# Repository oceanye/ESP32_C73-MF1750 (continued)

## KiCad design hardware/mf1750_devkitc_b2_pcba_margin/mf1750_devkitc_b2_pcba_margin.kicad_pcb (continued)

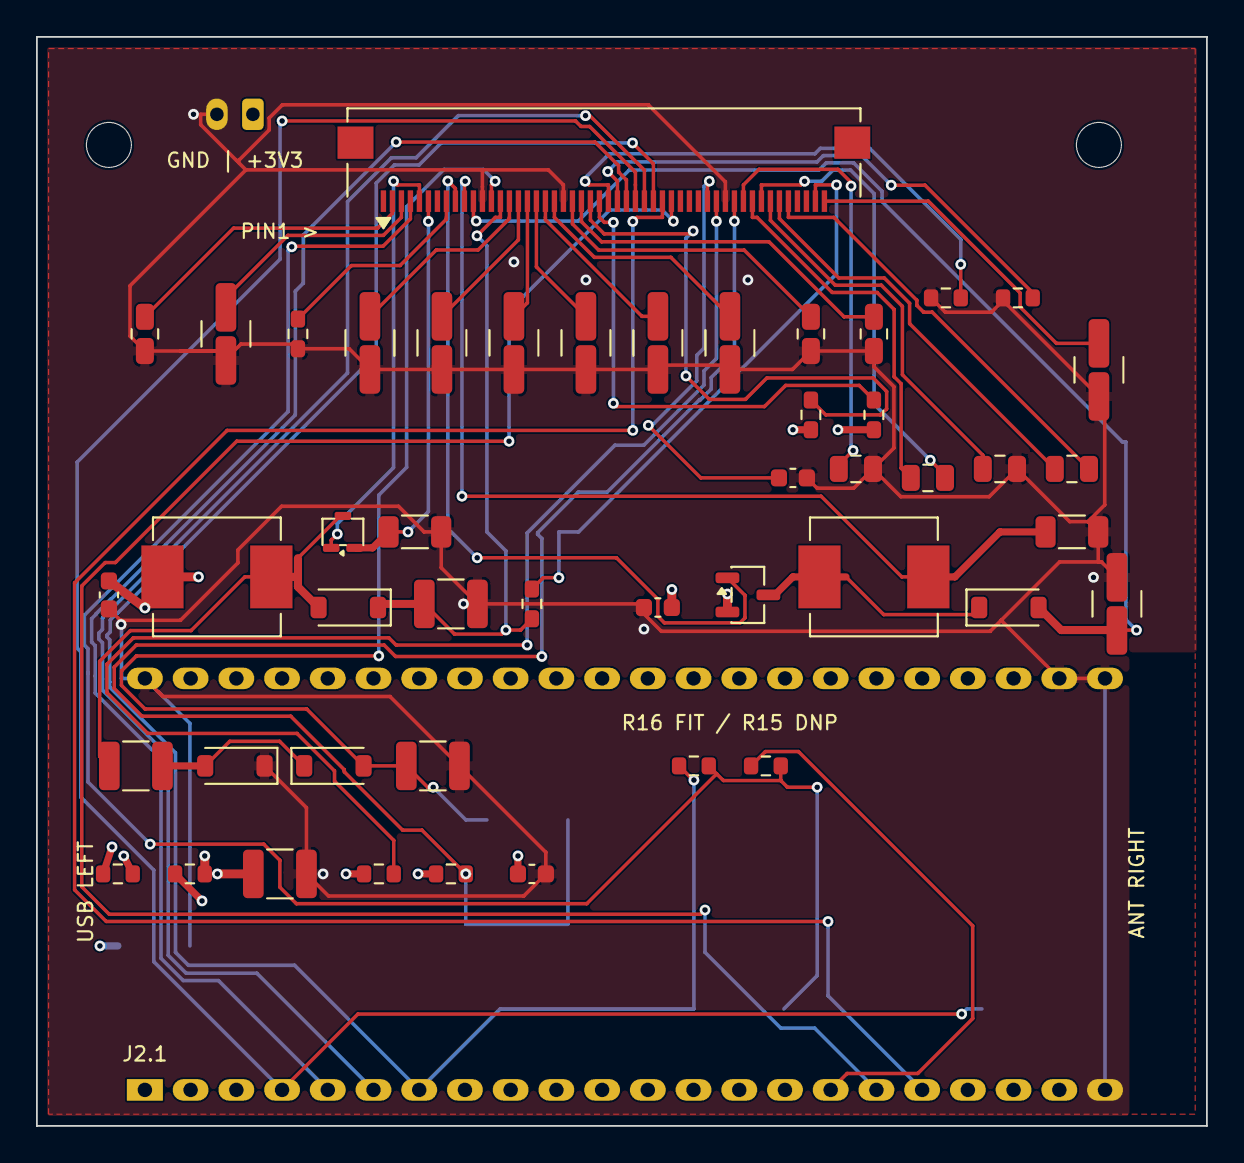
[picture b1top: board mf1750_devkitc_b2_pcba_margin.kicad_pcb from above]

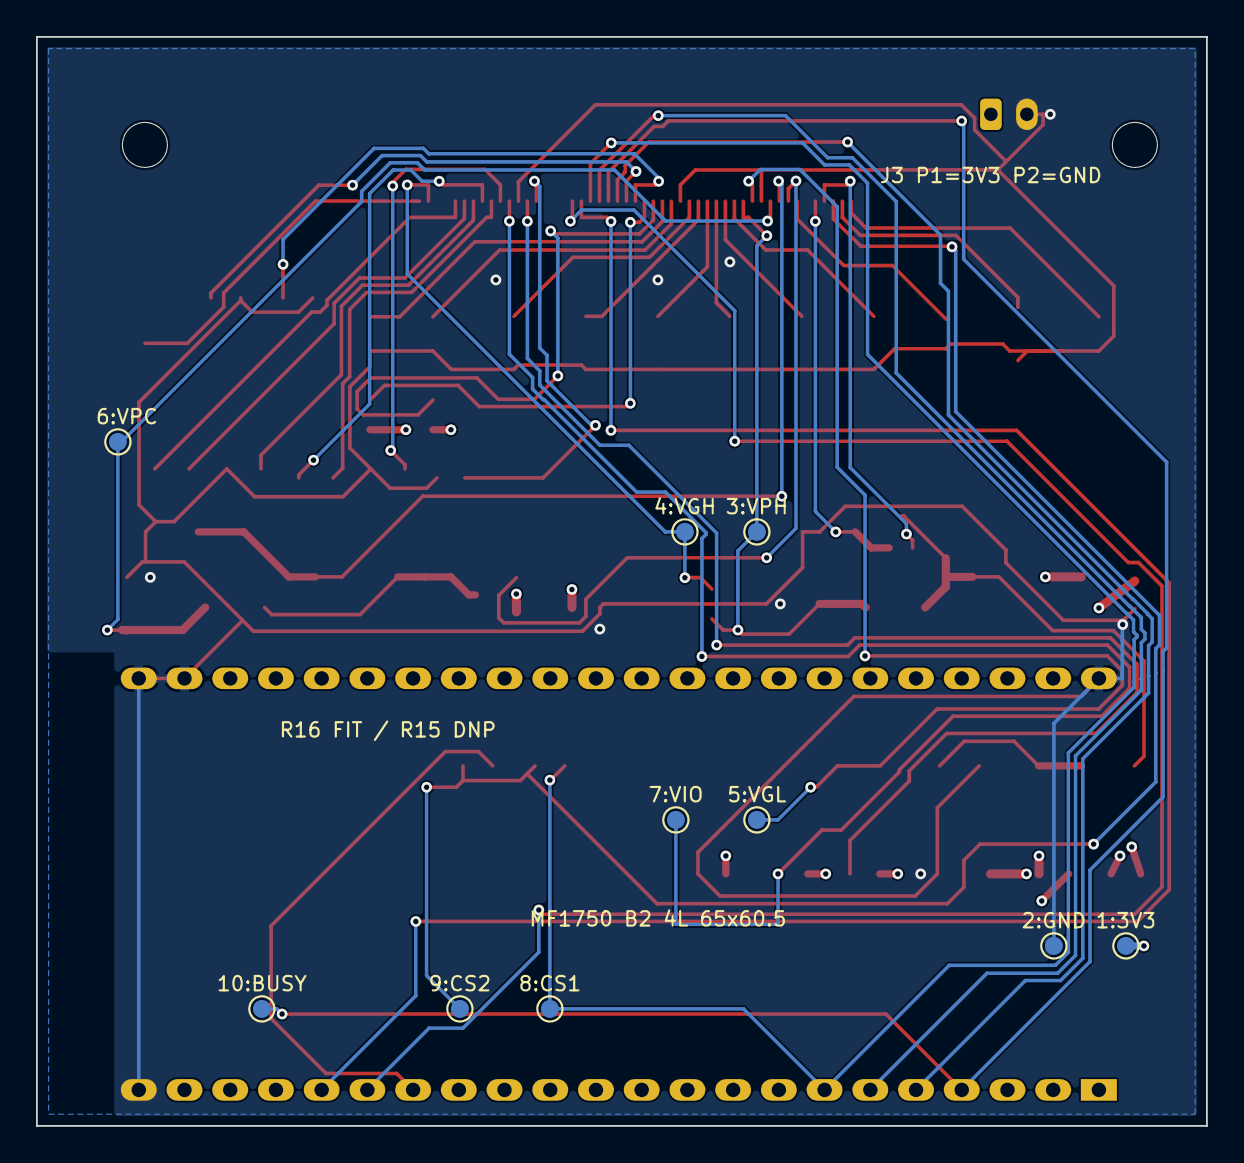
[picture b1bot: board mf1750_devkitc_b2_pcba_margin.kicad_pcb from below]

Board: 4 copper layers, 65.0 x 60.5 mm, 61 parts (10 on the bottom side), 48 nets.

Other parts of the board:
H1, H2: M2.5_NPTH; MountingHole_2.5mm

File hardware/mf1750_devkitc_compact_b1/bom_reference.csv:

Designator,Value,Footprint,LCSC Part #,Manufacturer,MPN,DNP,Note
J1,50pin 0.5mm dual-contact FPC,MF1750_Production:XUNPU_FPC-05FB-50PH20_1x50_P0.5mm_DualContact,C2856838,XUNPU,FPC-05FB-50PH20,No,Official JLC footprint; pin1 left in assembled-board top view
J2,ESP32-S3-DevKitC-1-N16R8 socket,MF1750_Compact:ESP32-S3-DevKitC-1_Socket,,Espressif,ESP32-S3-DevKitC-1-N16R8 + 2x 1x22 stacking female socket,Manual,Exact N16R8; 22.86 mm rows; installed board spacing >=11 mm; manual/DNP from SMT
J3,EPD 3V3 INPUT,Connector_JST:JST_PH_S2B-PH-K_1x02_P2.00mm_Horizontal,,JST,S2B-PH-K + PHR-2 housing + wire-gauge-matched PH crimp contacts,Manual,"Hand-fit keyed horizontal input; pin1=3V3, pin2=GND"
C0,4.7uF/25V/0603,Capacitor_SMD:C_0603_1608Metric,C69335,SAMSUNG,CL10A475KA8NQNC,No,
L1,15uH/3.1A SMMS0650,MF1750_Production:SXN_SMMS0650_7.1x6.6mm,C149585,SXN,SMMS0650-150M,No,
D1,MBR0530,Diode_SMD:D_SOD-123,C77336,JSCJ,MBR0530,No,pad1/K=VPH; pad2/A=SW_H
C2,10uF/25V/1210,Capacitor_SMD:C_1210_3225Metric,C2909422,Walsin,1210B106K250CT,No,
R5,0R,Resistor_SMD:R_0603_1608Metric,C21189,UNI-ROYAL,0603WAF0000T5E,No,
C4,10uF/25V/1210,Capacitor_SMD:C_1210_3225Metric,C2909422,Walsin,1210B106K250CT,No,
D2,MBR0530,Diode_SMD:D_SOD-123,C77336,JSCJ,MBR0530,No,pad1/K=GND; pad2/A=NEG_PUMP_H
D3,MBR0530,Diode_SMD:D_SOD-123,C77336,JSCJ,MBR0530,No,pad1/K=NEG_PUMP_H; pad2/A=PREVGL
C5,10uF/25V/1210,Capacitor_SMD:C_1210_3225Metric,C2909422,Walsin,1210B106K250CT,No,
R1,0.2R 0.2W 1%,Resistor_SMD:R_1206_3216Metric,C2907350,FOJAN,FRL1206FR200TS,No,
C22,4.7uF/25V/0603,Capacitor_SMD:C_0603_1608Metric,C69335,SAMSUNG,CL10A475KA8NQNC,No,
L2,15uH/3.1A SMMS0650,MF1750_Production:SXN_SMMS0650_7.1x6.6mm,C149585,SXN,SMMS0650-150M,No,
D4,MBR0530,Diode_SMD:D_SOD-123,C77336,JSCJ,MBR0530,No,pad1/K=SW_C; pad2/A=VPC
C6,10uF/25V/1210,Capacitor_SMD:C_1210_3225Metric,C2909422,Walsin,1210B106K250CT,No,
R3,0.22R 0.2W 1%,Resistor_SMD:R_1206_3216Metric,C3017221,VO,SCR1206FR220,No,
R4,0R,Resistor_SMD:R_0603_1608Metric,C21189,UNI-ROYAL,0603WAF0000T5E,No,FIT; J3 external EPD 3V3 to EPD_3V3
R8,0R,Resistor_SMD:R_0603_1608Metric,C21189,UNI-ROYAL,0603WAF0000T5E,No,FIT; J3 external EPD 3V3 to V_B
C23,10uF/25V/1210,Capacitor_SMD:C_1210_3225Metric,C2909422,Walsin,1210B106K250CT,No,
R6,0R,Resistor_SMD:R_0603_1608Metric,C21189,UNI-ROYAL,0603WAF0000T5E,No,
R7,0R,Resistor_SMD:R_0603_1608Metric,C21189,UNI-ROYAL,0603WAF0000T5E,No,
C3,0.1uF/50V/0603,Capacitor_SMD:C_0603_1608Metric,C14663,YAGEO,CC0603KRX7R9BB104,No,
R9,4.7k 1%,Resistor_SMD:R_0603_1608Metric,C23162,UNI-ROYAL,0603WAF4701T5E,No,
R10,4.7k 1%,Resistor_SMD:R_0603_1608Metric,C23162,UNI-ROYAL,0603WAF4701T5E,No,
R12,0R,Resistor_SMD:R_0603_1608Metric,C21189,UNI-ROYAL,0603WAF0000T5E,No,"populate: BS0 low, 4-wire"
R13,0R,Resistor_SMD:R_0603_1608Metric,C21189,UNI-ROYAL,0603WAF0000T5E,No,"populate: BS1 low, 4-wire"
C13,4.7uF/10V/0805,Capacitor_SMD:C_0805_2012Metric,C87998,SAMSUNG,CL21B475KPFNNNE,No,
C14,0.47uF/50V/1210,Capacitor_SMD:C_1210_3225Metric,C309505,YAGEO,CC1210KKX7R9BB474,No,
R2,0R,Resistor_SMD:R_0603_1608Metric,C21189,UNI-ROYAL,0603WAF0000T5E,No,
C7,10uF/25V/1210,Capacitor_SMD:C_1210_3225Metric,C2909422,Walsin,1210B106K250CT,No,
C8,10uF/25V/1210,Capacitor_SMD:C_1210_3225Metric,C2909422,Walsin,1210B106K250CT,No,
C9,10uF/25V/1210,Capacitor_SMD:C_1210_3225Metric,C2909422,Walsin,1210B106K250CT,No,
C10,10uF/25V/1210,Capacitor_SMD:C_1210_3225Metric,C2909422,Walsin,1210B106K250CT,No,
C11,10uF/25V/1210,Capacitor_SMD:C_1210_3225Metric,C2909422,Walsin,1210B106K250CT,No,
C12,10uF/25V/1210,Capacitor_SMD:C_1210_3225Metric,C2909422,Walsin,1210B106K250CT,No,
C21,1uF/50V/0805,Capacitor_SMD:C_0805_2012Metric,C28323,SAMSUNG,CL21B105KBFNNNE,No,
C20,1uF/50V/0805,Capacitor_SMD:C_0805_2012Metric,C28323,SAMSUNG,CL21B105KBFNNNE,No,
C1,2.2uF/25V/0603,Capacitor_SMD:C_0603_1608Metric,C415535,Murata,GRM188Z71E225KE43D,No,
C19,1uF/50V/0805,Capacitor_SMD:C_0805_2012Metric,C28323,SAMSUNG,CL21B105KBFNNNE,No,
C18,1uF/50V/0805,Capacitor_SMD:C_0805_2012Metric,C28323,SAMSUNG,CL21B105KBFNNNE,No,
C17,1uF/50V/0805,Capacitor_SMD:C_0805_2012Metric,C28323,SAMSUNG,CL21B105KBFNNNE,No,
C16,1uF/50V/0805,Capacitor_SMD:C_0805_2012Metric,C28323,SAMSUNG,CL21B105KBFNNNE,No,
C15,0.47uF/50V/1210,Capacitor_SMD:C_1210_3225Metric,C309505,YAGEO,CC1210KKX7R9BB474,No,
R15,0R DNP,Resistor_SMD:R_0603_1608Metric,C21189,UNI-ROYAL,0603WAF0000T5E,Yes,DNP; do not fit with R16
R16,0R,Resistor_SMD:R_0603_1608Metric,C21189,UNI-ROYAL,0603WAF0000T5E,No,FIT; verified independent CS2 to SL_CSB
Q1,Si1308EDL,Package_TO_SOT_SMD:SOT-323_SC-70,C3289597,Vishay,SI1308EDL-T1-BE3,No,"Vishay Si1308EDL SC-70 top view: pin1=G, pin2=S, pin3=D; reference-selected part, RDS(on) is a controlled A1 numerical deviation"
Q2,AO3401A,Package_TO_SOT_SMD:SOT-23-3,C15127,AOS,AO3401A,No,"SOT-23: pin1=G, pin2=S, pin3=D"
TP1,3V3,TestPoint:TestPoint_Pad_D1.0mm,,,,Manual,Bottom-side measurement pad only; never use as the panel supply connector
TP2,GND,TestPoint:TestPoint_Pad_D1.0mm,,,,Manual,Bottom-side measurement pad only; never use as the panel supply connector
TP3,VPH,TestPoint:TestPoint_Pad_D1.0mm,,,,Manual,test pad only
TP4,PREVGH,TestPoint:TestPoint_Pad_D1.0mm,,,,Manual,test pad only
TP5,PREVGL,TestPoint:TestPoint_Pad_D1.0mm,,,,Manual,test pad only
TP6,VPC,TestPoint:TestPoint_Pad_D1.0mm,,,,Manual,test pad only
TP7,VDDIO,TestPoint:TestPoint_Pad_D1.0mm,,,,Manual,test pad only
TP8,CSB,TestPoint:TestPoint_Pad_D1.0mm,,,,Manual,test pad only
TP9,SL_CSB,TestPoint:TestPoint_Pad_D1.0mm,,,,Manual,test pad only
TP10,BUSY_N,TestPoint:TestPoint_Pad_D1.0mm,,,,Manual,test pad only
"H1,H2",M2.5 NPTH,MountingHole:MountingHole_2.5mm,,,,Manual,mechanical

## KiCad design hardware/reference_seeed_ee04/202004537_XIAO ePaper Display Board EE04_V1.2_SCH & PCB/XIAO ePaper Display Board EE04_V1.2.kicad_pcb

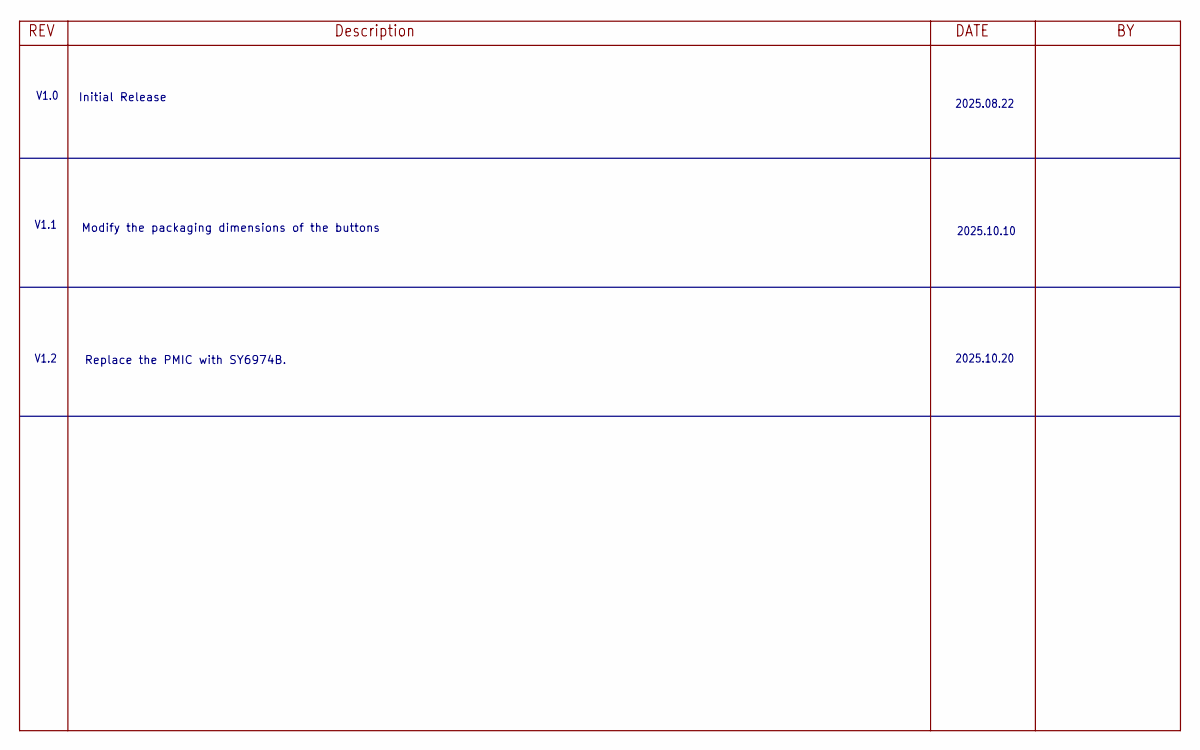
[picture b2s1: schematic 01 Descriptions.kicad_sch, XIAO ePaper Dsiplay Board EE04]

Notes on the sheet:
2025.08.22
2025.10.20
2025.10.10
Modify the packaging dimensions of the buttons
Replace the PMIC with SY6974B.
V1.1
Initial Release
V1.0
V1.2

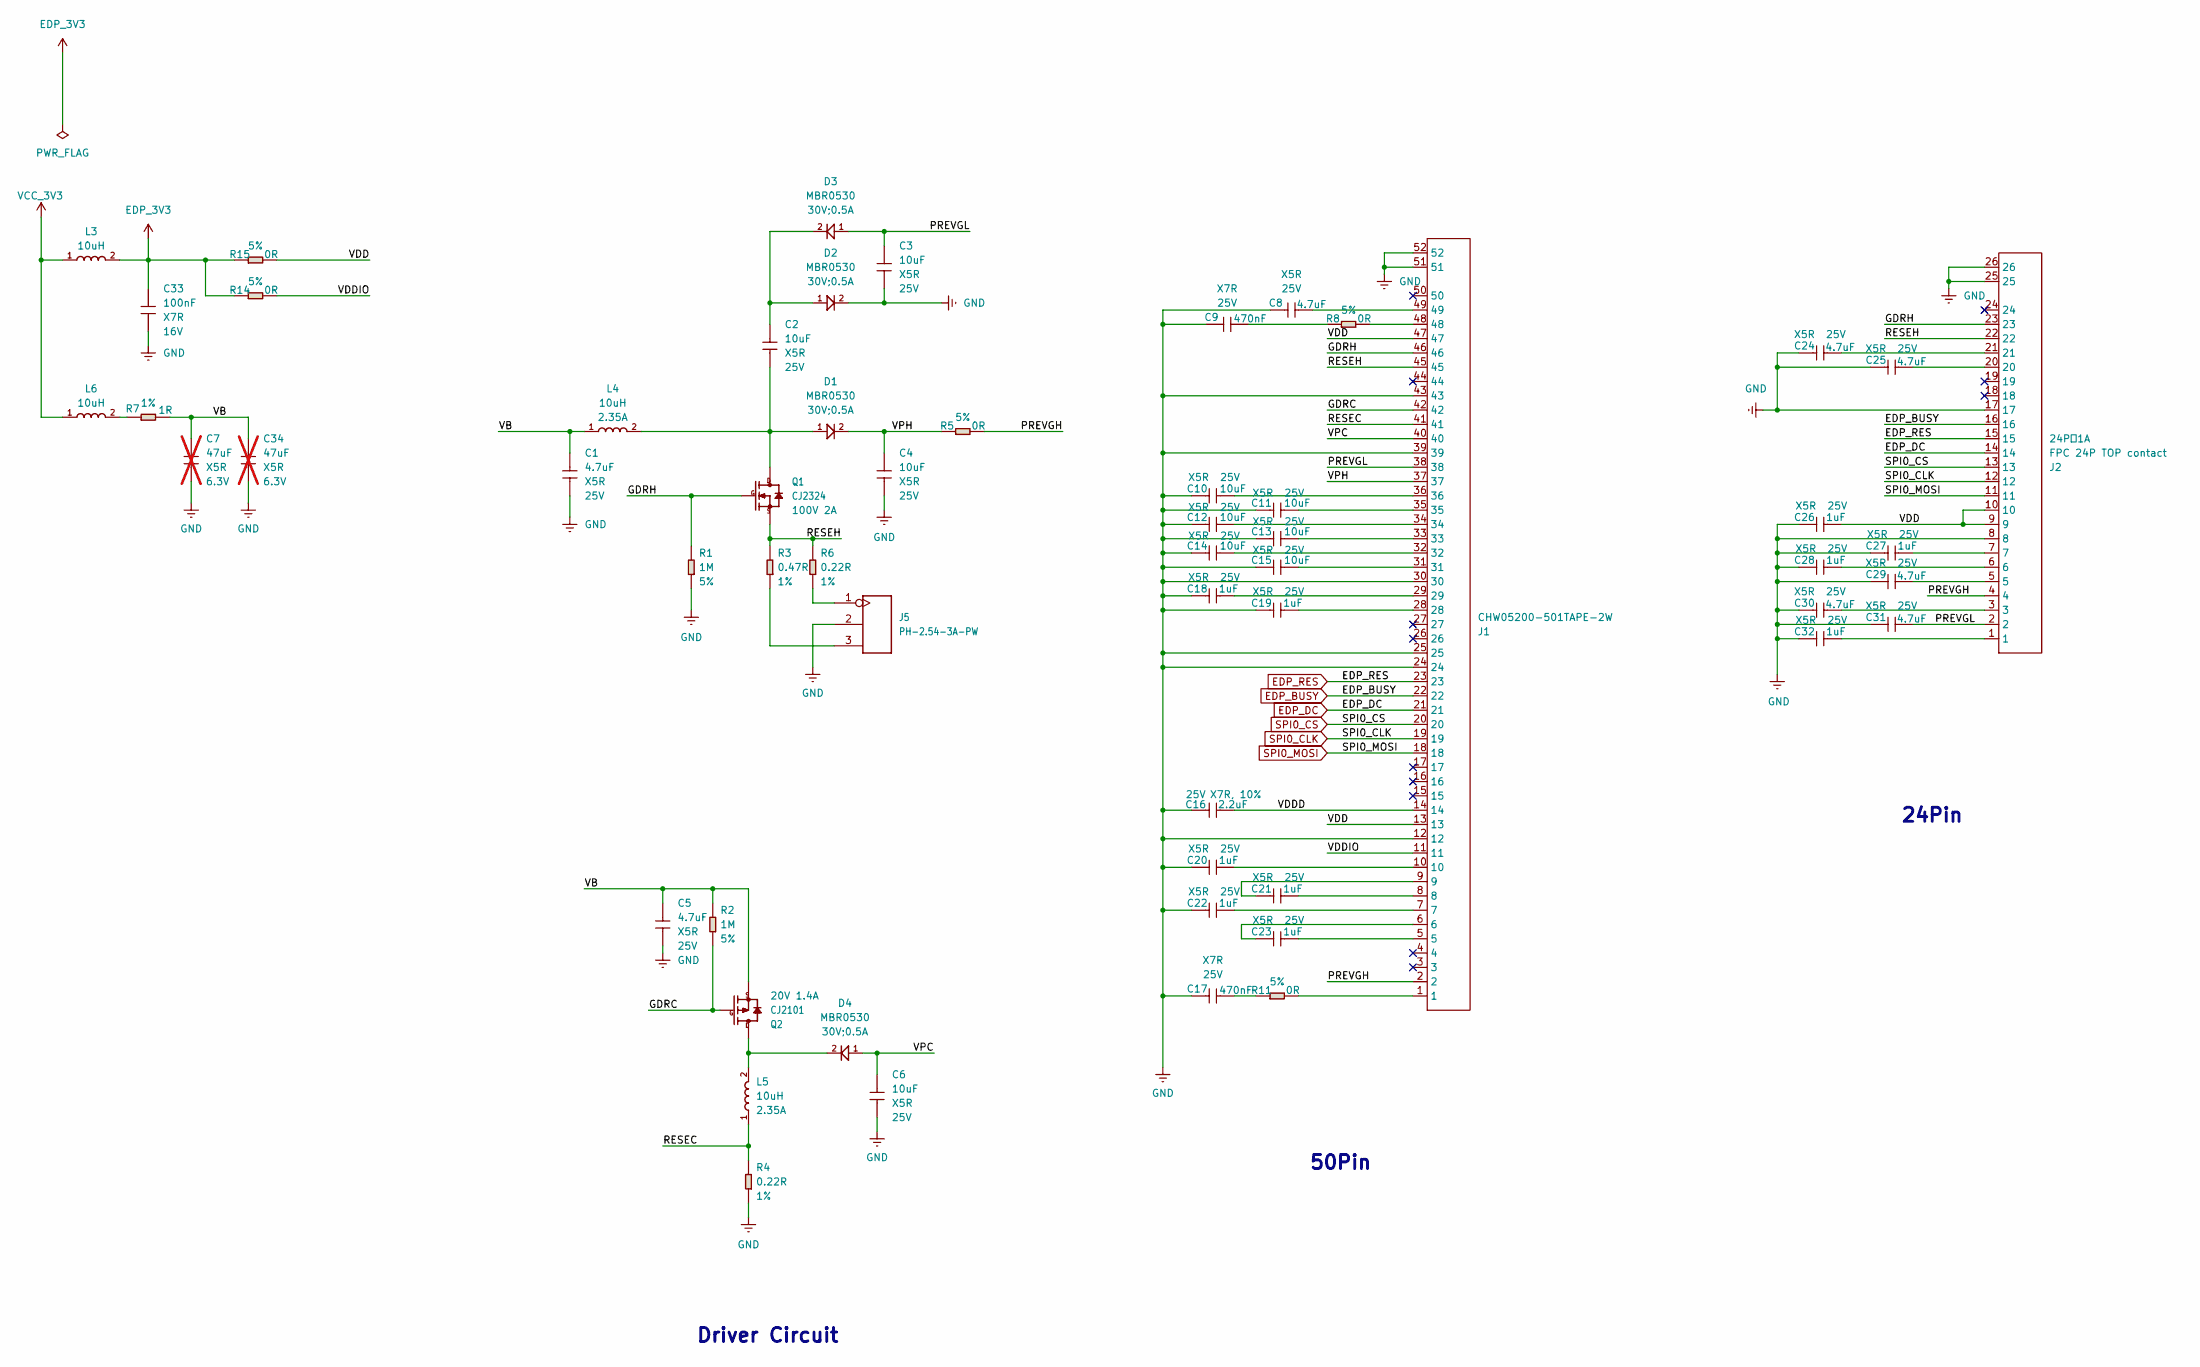
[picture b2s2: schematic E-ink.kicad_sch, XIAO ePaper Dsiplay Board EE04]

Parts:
C1, C5, C8, C24, C25, C29, C30, C31: 4.7uF; C0805; Voltage Rating 25V; MPN CC0805KKX5R8BB475
C2, C3, C4, C6, C10, C11, C12, C13, C14, C15: 10uF; C0805; Voltage Rating 25V; MPN CC0805KKX5R8BB106
C7, C34: 47uF; C0805; Voltage Rating 6.3V; MPN CC0805MKX5R5BB476; not fitted
C9, C17: 470nF; C0603; Voltage Rating 25V; MPN CC0603KRX7R8BB474
C16: 2.2uF; C0805; Voltage Rating 25V; MPN CC0805KKX7R8BB225
C18, C19, C20, C21, C22, C23, C26, C27, C28, C32: 1uF; C0402; Voltage Rating 25V; MPN CC0402KRX5R8BB105
C33: 100nF; C0402; Voltage Rating 16V; MPN CC0402KRX7R7BB104
D1, D2, D3, D4: MBR0530; SOD-123; Rating 30V;0.5A; MPN MBR0530
J1: CHW05200-501TAPE-2W; FPC50-0.5-28.6X4.9X2MM; MPN CHW05200-501TAPE-2W
J2: FPC 24P TOP contact; FPC24-0.5-15.5X4.9X2MM; Rating 24P，1A; MPN FPC0.5K-DH-24WB
J5: PH-2.54-3A-PW; H3-2.54-90D; MPN PH-2.54-3A-PW
L3, L6: 10uH; L0603; MPN MWSD1608FE100KT
L4, L5: 10uH; L5040S; Rating 2.35A; MPN SWPA5040S100MT
Q1: CJ2324; SOT23; Rating 100V 2A; MPN CJ2324
Q2: CJ2101; SOT-323; Rating 20V 1.4A; MPN CJ2101
R1, R2: 1M; R0402; Power Rating 5%; MPN RC0402JR-071ML
R3: 0.47R; R0603; Power Rating 1%; MPN RL0603FR-070R47L
R4, R6: 0.22R; R0805; Power Rating 1%; MPN RL0805FR-7W0R22L
R5, R8, R11, R14, R15: 0R; R0603; Power Rating 5%; MPN RC0603JR-070RL
R7: 1R; R0805; Power Rating 1%; MPN RC0805FR-071RL

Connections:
/E-ink/GDRC: J1.42, Q2.1 (G), R2.1
/E-ink/GDRH: J1.46, J2.23, Q1.1 (G), R1.2
/E-ink/PREVGH: J1.2, J2.4, R5.2
/E-ink/PREVGL: C3.2, C31.2, D3.1, J1.38, J2.2
/E-ink/RESEC: J1.41, L5.1, R4.2
/E-ink/RESEH: J1.45, J2.22, Q1.2 (S), R3.2, R6.2
/E-ink/VB: C1.1, C5.1, C7.1, C34.1, L4.1, Q2.2 (S), R2.2, R7.2
/E-ink/VDD: C26.2, J1.13, J1.47, J2.9, J2.10, R15.2
/E-ink/VDDD: C16.2, J1.14
/E-ink/VDDIO: J1.11, R14.2
/E-ink/VPC: C6.2, D4.1, J1.40
/E-ink/VPH: C4.2, D1.2, J1.37, R5.1
EDP_3V3: C33.1, L3.2, R14.1, R15.1
EDP_BUSY: J1.22, J2.16; also elsewhere on the board
EDP_DC: J1.21, J2.14; also elsewhere on the board
EDP_RES: J1.23, J2.15; also elsewhere on the board
GND: C1.2, C3.1, C4.1, C5.2, C6.1, C7.2, C8.1, C9.1, C10.2, C11.2, C12.2, C13.2, C14.2, C15.2, C16.1, C17.1, C18.1, C19.1, C20.1, C22.1, C24.1, C25.1, C26.1, C27.1, C28.1, C29.1, C30.1, C31.1, C32.1, C33.2, C34.2, D2.2, J1.12, J1.24, J1.25, J1.30, J1.39, J1.43, J1.51, J1.52, J2.8, J2.17, J2.25, J2.26, J5.2, R1.1, R4.1; also elsewhere on the board
unnamed: C2.2, D2.1, D3.2
unnamed: C8.2, J1.49
unnamed: C9.2, R8.1
unnamed: C10.1, J1.36
unnamed: C11.1, J1.35
unnamed: C12.1, J1.34
unnamed: C13.1, J1.33
unnamed: C14.1, J1.32
unnamed: C15.1, J1.31
unnamed: C17.2, R11.1
unnamed: C18.2, J1.29
unnamed: C19.2, J1.28
unnamed: C20.2, J1.10
unnamed: C21.1, J1.9
unnamed: C21.2, J1.8
unnamed: C22.2, J1.7
unnamed: C23.1, J1.6
unnamed: C23.2, J1.5
unnamed: C24.2, J2.21
unnamed: C25.2, J2.20
unnamed: C27.2, J2.7
unnamed: C28.2, J2.6
unnamed: C29.2, J2.5
unnamed: C30.2, J2.3
unnamed: C32.2, J2.1
unnamed: J1.1, R11.2
unnamed: J1.48, R8.2
unnamed: J5.1, R6.1
unnamed: J5.3, R3.1
unnamed: L6.2, R7.1
unnamed: C2.1, D1.1, L4.2, Q1.3 (D)
unnamed: D4.2, L5.2, Q2.3 (D)
SPI0_CLK: J1.19, J2.12; also elsewhere on the board
SPI0_CS: J1.20, J2.13; also elsewhere on the board
SPI0_MOSI: J1.18, J2.11; also elsewhere on the board
VCC_3V3: L3.1, L6.1; also elsewhere on the board

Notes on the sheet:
Driver Circuit
24Pin
50Pin

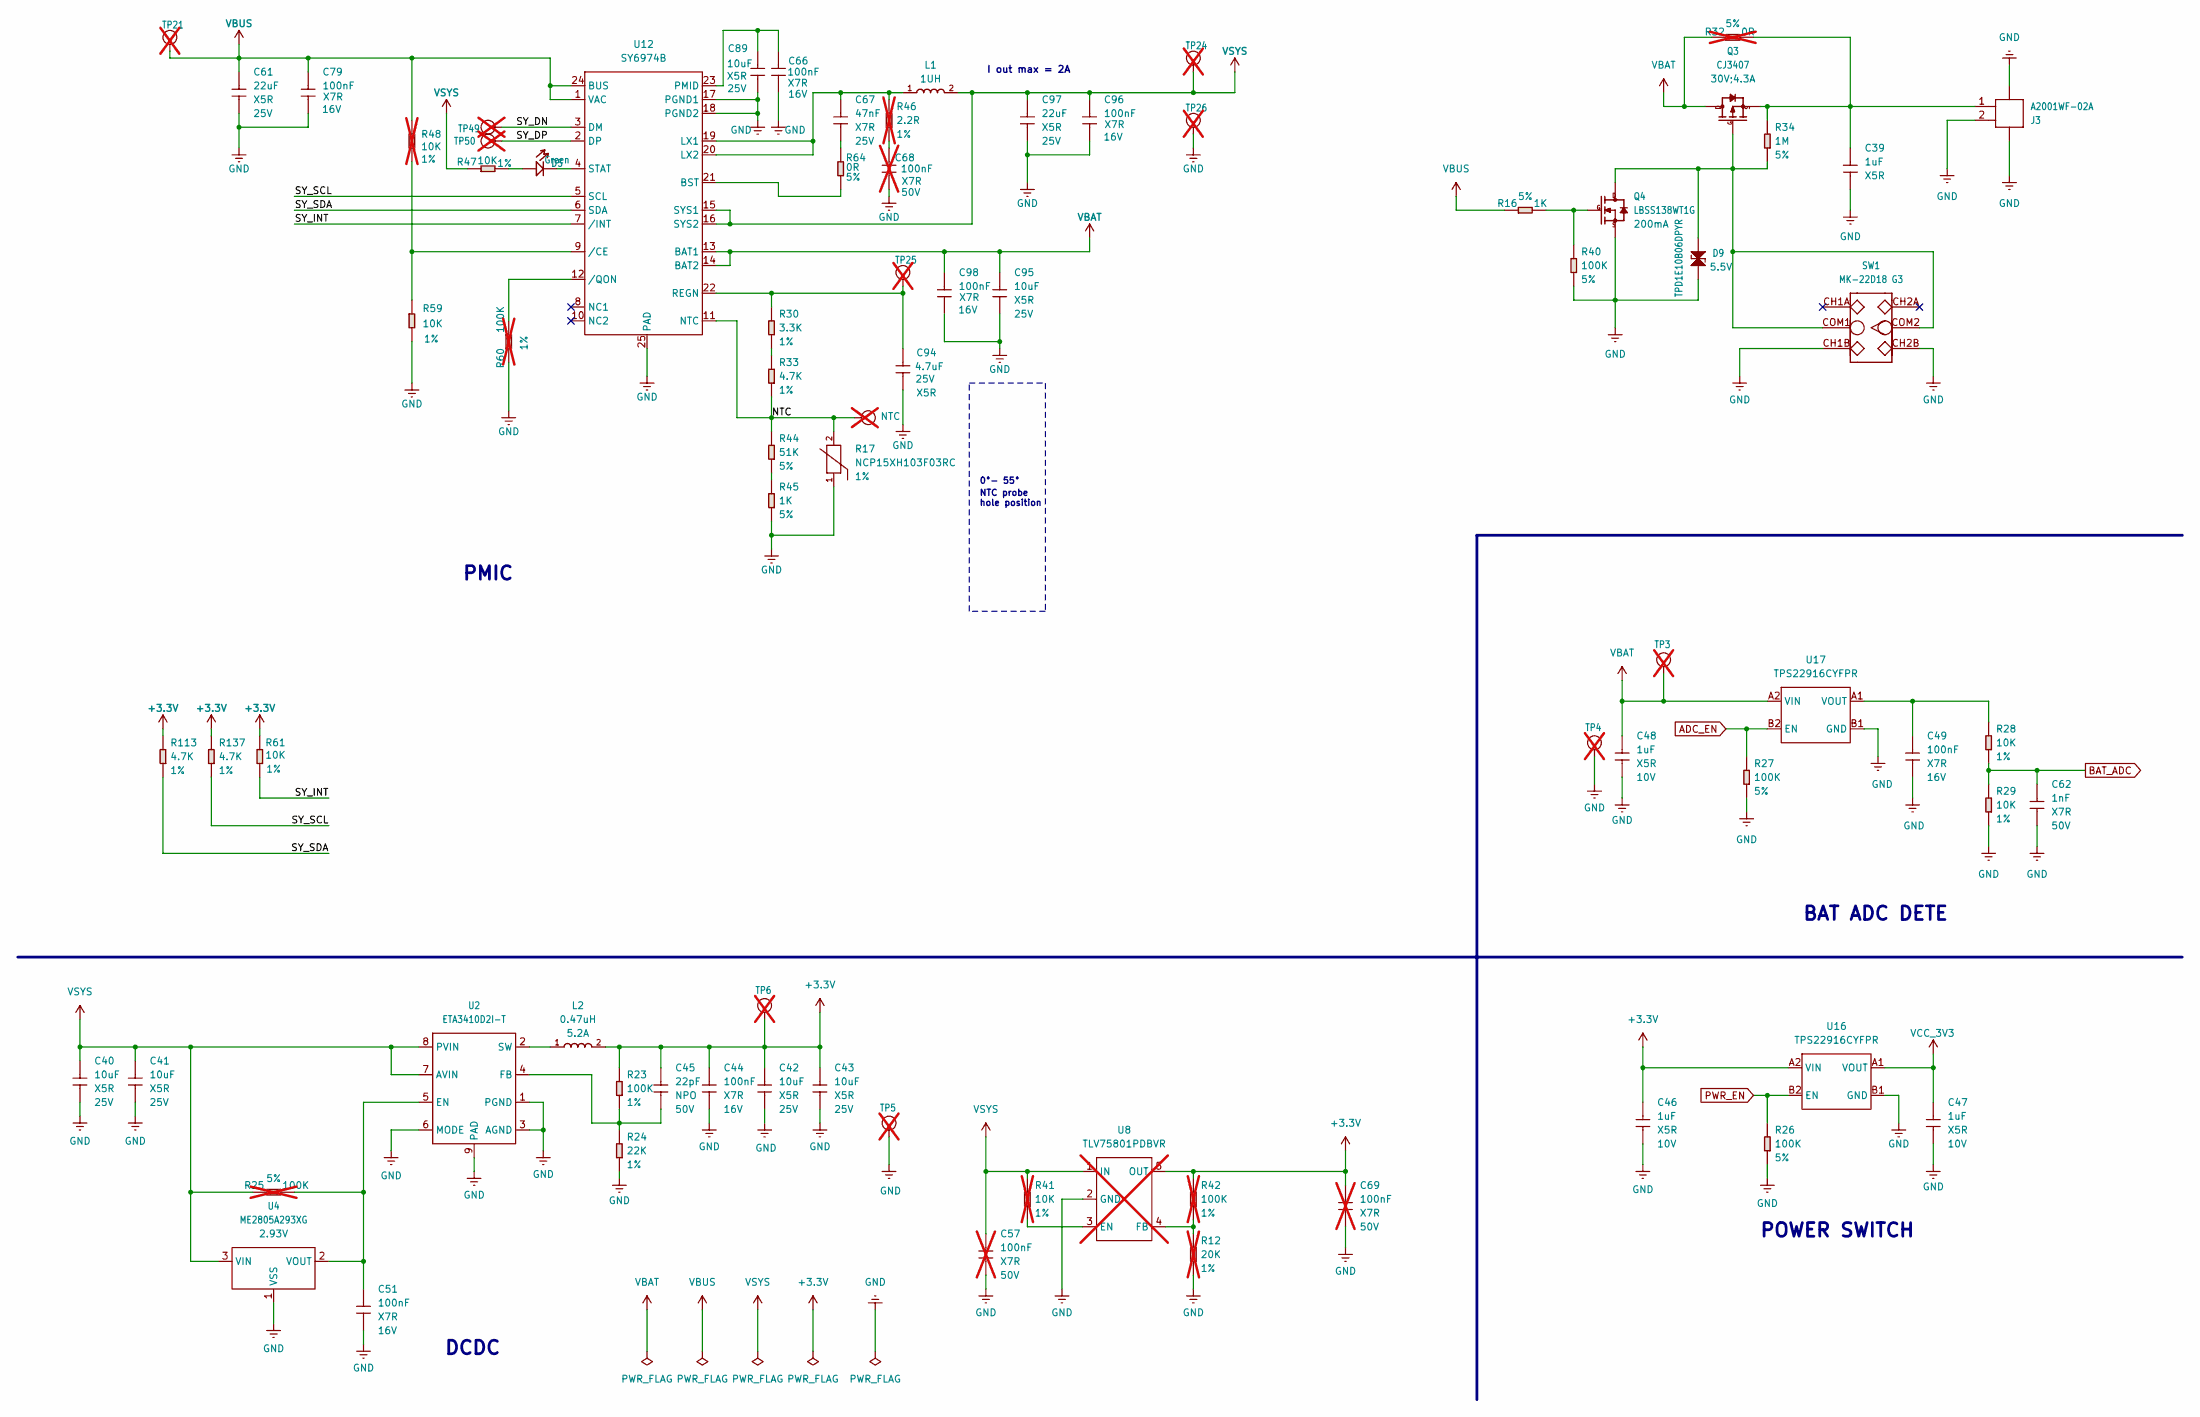
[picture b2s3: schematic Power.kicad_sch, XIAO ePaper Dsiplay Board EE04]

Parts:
C39, C46, C47, C48: 1uF; C0402; Voltage Rating 10V; MPN CC0402KRX5R6BB105
C40, C41, C42, C43, C89, C95: 10uF; C0805; Voltage Rating 25V; MPN CC0805KKX5R8BB106
C44, C49, C51, C66, C79, C96, C98: 100nF; C0402; Voltage Rating 16V; MPN CC0402KRX7R7BB104
C45: 22pF; C0402; Voltage Rating 50V; MPN CC0402JRNPO9BN220
C57, C68, C69: 100nF; C0603; Voltage Rating 50V; MPN CC0603KRX7R9BB104; not fitted
C61, C97: 22uF; C0805; Voltage Rating 25V; MPN CC0805MKX5R8BB226
C62: 1nF; C0402; Voltage Rating 50V; MPN CC0402KRX7R9BB102
C67: 47nF; C0402; Voltage Rating 25V; MPN CC0402KRX7R8BB473
C94: 4.7uF; C0805; Voltage Rating 25V; MPN CC0805KKX5R8BB475
D5: Green; LED2-0.6X1.7MM; MPN 27-21/GHC-YR1S2M/3C
D9: TPD1E10B06DPYR; ESD-0402; Rating 5.5V; MPN TPD1E10B06DPYR
J3: A2001WF-02A; JST2+2P_2.0_PH_S2B-PH-SM4-TB_1x02-1MP_Horizontal; MPN A2001WF-02A
L1: 1UH; INT2-SMD-4.2X4.4X1.8MM; MPN MWSA0402S-1R0MT
L2: 0.47uH; L0805; Rating 5.2A; MPN WPN201610MR47MT
NTC_IN2: NTC; TP-D45MIL; Part Type Test Point; not fitted
Q3: CJ3407; SOT23; Rating 30V;4.3A; MPN CJ3407
Q4: LBSS138WT1G; SOT-323; Rating 200mA; MPN LBSS138WT1G
R12: 20K; R0402; Power Rating 1%; MPN RC0402FR-0720KL; not fitted
R16, R45: 1K; R0402; Power Rating 5%; MPN RC0402JR-071KL
R17: NCP15XH103F03RC; R0402; Power Rating 1%; MPN NCP15XH103F03RC
R23: 100K; R0402; Power Rating 1%; MPN RC0402FR-07100KL
R24: 22K; R0402; Power Rating 1%; MPN RC0402FR-0722KL
R25: 100K; R0402; Power Rating 5%; MPN RC0402JR-07100KL; not fitted
R26, R27, R40: 100K; R0402; Power Rating 5%; MPN RC0402JR-07100KL
R28, R29, R47, R59, R61: 10K; R0402; Power Rating 1%; MPN RC0402FR-0710KL
R30: 3.3K; R0402; Power Rating 1%; MPN RC0402JR-073K3L
R32: 0R; R0603; Power Rating 5%; MPN RC0603JR-070RL; not fitted
R33, R113, R137: 4.7K; R0402; Power Rating 1%; MPN RC0402FR-074K7L
R34: 1M; R0402; Power Rating 5%; MPN RC0402JR-071ML
R41, R48: 10K; R0402; Power Rating 1%; MPN RC0402FR-0710KL; not fitted
R42, R60: 100K; R0402; Power Rating 1%; MPN RC0402FR-07100KL; not fitted
R44: 51K; R0402; Power Rating 5%; MPN RC0402JR-0751KL
R46: 2.2R; R0603; Power Rating 1%; MPN RC0603FR-072R2L; not fitted
R64: 0R; R0402; Power Rating 5%; MPN RC0402JR-070RL
SW1: MK-22D18 G3; SW6-2CH-2.54-9X3.5X3.5; MPN MK-22D18 G3
TP3, TP4, TP5, TP6, TP21, TP24, TP25, TP26, TP49, TP50: Test Point; TP-D45MIL; Part Type Test Point; not fitted
U2: ETA3410D2I-T; DFN8G-0.5-2X2MM; MPN ETA3410D2I-T
U4: ME2805A293XG; SOT-23; Rating 2.93V; MPN ME2805A293XG
U8: TLV75801PDBVR; SOT-23-5; MPN TLV75801PDBVR; not fitted
U12: SY6974B; QFN24G-0.5-4X4MM; MPN SY6974B
U16, U17: TPS22916CYFPR; WLCSP4-0.4-0.77X0.77X0.33MM; MPN TPS22916CYFPR

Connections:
+3.3V: C42.2, C43.2, C44.1, C45.1, C46.1, C69.1, L2.2, R23.2, R42.2, R61.2, R113.2, R137.2, TP6.1 (T), U8.5 (OUT), U16.A2 (VIN)
/Power/NTC: NTC_IN2.1 (T), R17.2, R33.1, R44.2, U12.11 (NTC)
/Power/SY_DN: TP49.1 (T), U12.3 (DM)
/Power/SY_DP: TP50.1 (T), U12.2 (DP)
/Power/SY_INT: R61.1, U12.7 (/INT)
/Power/SY_SCL: R137.1, U12.5 (SCL)
/Power/SY_SDA: R113.1, U12.6 (SDA)
ADC_EN: R27.2, U17.B2 (EN); also elsewhere on the board
BAT_ADC: C62.1, R28.1, R29.2; also elsewhere on the board
GND: C39.2, C40.1, C41.1, C42.1, C43.1, C44.2, C46.2, C47.2, C48.2, C49.2, C51.2, C57.2, C61.2, C62.2, C66.1, C68.1, C69.2, C79.2, C89.1, C94.2, C95.2, C96.2, C97.2, C98.2, D9.1, J3.2, J3.3, J3.4, Q4.2 (S), R12.1, R17.1, R24.1, R26.1, R27.1, R29.1, R40.1, R45.1, R59.2, R60.2, SW1.CH1B, SW1.CH2B, TP4.1 (T), TP5.1 (T), TP26.1 (T), U2.1 (PGND), U2.3 (AGND), U2.6 (MODE), U2.9 (PAD), U4.1 (VSS), U8.2 (GND), U12.17 (PGND1), U12.18 (PGND2), U12.25 (PAD), U16.B1 (GND), U17.B1 (GND); also elsewhere on the board
unnamed: C67.2, R64.2
unnamed: C68.2, R46.1
unnamed: D5.1 (+), R47.2
unnamed: D5.2 (-), U12.4 (STAT)
unnamed: D9.2, Q3.1 (G), Q4.3 (D), R34.1, SW1.COM1, SW1.COM2
unnamed: C39.1, J3.1, Q3.2 (S), R32.2, R34.2
unnamed: Q4.1 (G), R16.2, R40.2
unnamed: R30.1, R33.2
unnamed: R44.1, R45.2
unnamed: C94.1, R30.2, TP25.1 (T), U12.22 (REGN)
unnamed: C51.1, R25.1, U2.5 (EN), U4.2 (VOUT)
unnamed: C45.2, R23.1, R24.2, U2.4 (FB)
unnamed: L2.1, U2.2 (SW)
unnamed: R41.1, U8.3 (EN)
unnamed: R12.2, R42.1, U8.4 (FB)
unnamed: R64.1, U12.21 (BST)
unnamed: C67.1, L1.1, R46.2, U12.19 (LX1), U12.20 (LX2)
unnamed: C66.2, C89.2, U12.23 (PMID)
unnamed: R48.1, R59.1, U12.9 (/CE)
unnamed: R60.1, U12.12 (/QON)
unnamed: C49.1, R28.2, U17.A1 (VOUT)
PWR_EN: R26.2, U16.B2 (EN); also elsewhere on the board
VBAT: C48.1, C95.1, C98.1, Q3.3 (D), R32.1, TP3.1 (T), U12.13 (BAT1), U12.14 (BAT2), U17.A2 (VIN); also elsewhere on the board
VBUS: C61.1, C79.1, R16.1, R48.2, TP21.1 (T), U12.1 (VAC), U12.24 (BUS); also elsewhere on the board
VCC_3V3: C47.1, U16.A1 (VOUT); also elsewhere on the board
VSYS: C40.2, C41.2, C57.1, C96.1, C97.1, L1.2, R25.2, R41.2, R47.1, TP24.1 (T), U2.7 (AVIN), U2.8 (PVIN), U4.3 (VIN), U8.1 (IN), U12.15 (SYS1), U12.16 (SYS2)

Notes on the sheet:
PMIC
DCDC
BAT ADC DETE
POWER SWITCH
0°- 55°
I out max = 2A
NTC probe hole position
